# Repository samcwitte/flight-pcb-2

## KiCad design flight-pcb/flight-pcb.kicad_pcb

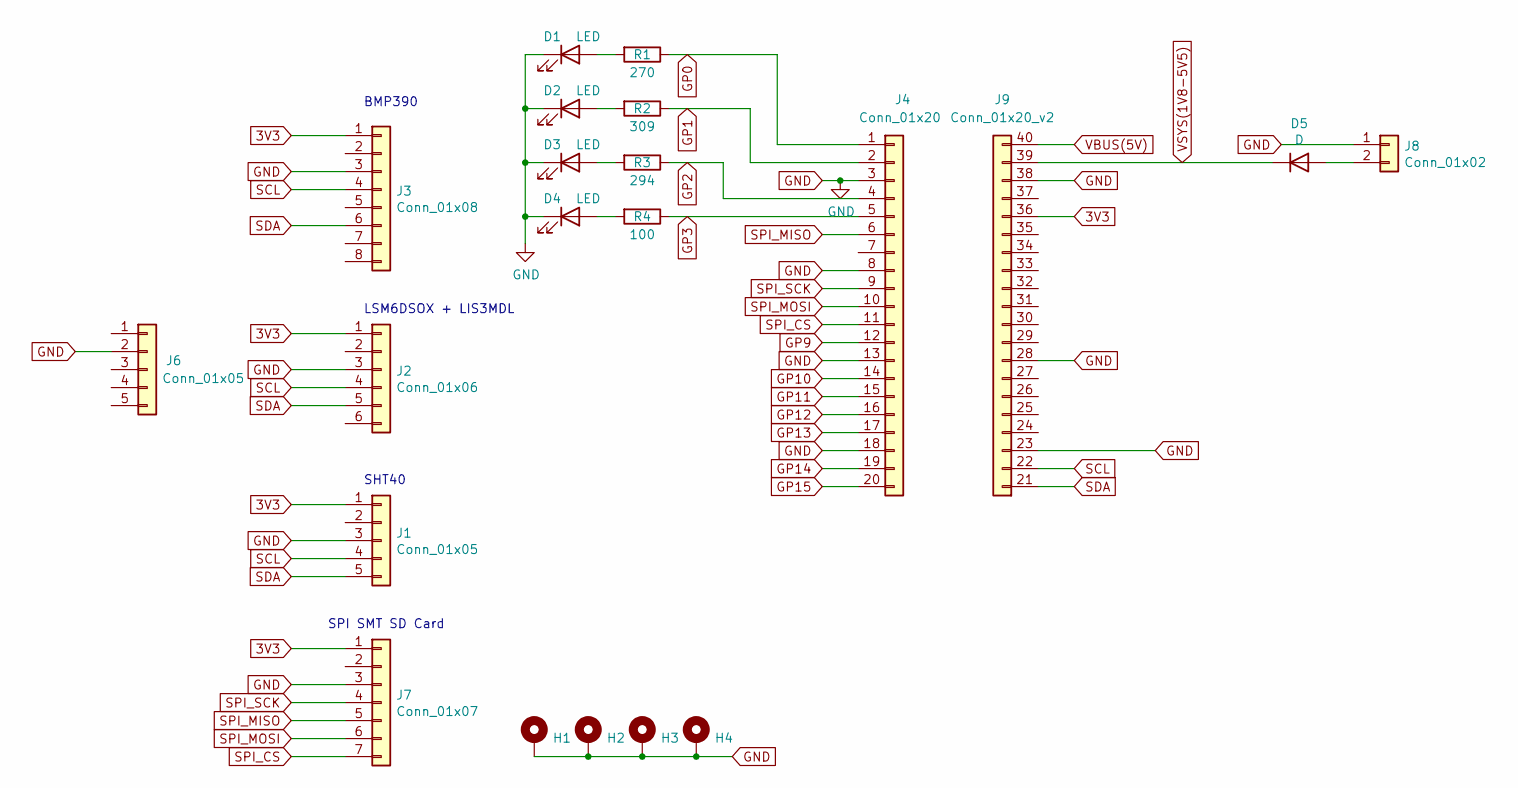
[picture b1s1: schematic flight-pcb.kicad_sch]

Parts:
D1, D2, D3, D4: LED; LED_0603_1608Metric
D5: D; D_SOD-123F
H1, H2, H3, H4: MountingHole_Pad; MountingHole_2.5mm_Pad
J1, J6: Conn_01x05; PinHeader_1x05_P2.54mm_Vertical
J2: Conn_01x06; PinHeader_1x06_P2.54mm_Vertical
J3: Conn_01x08; PinHeader_1x08_P2.54mm_Vertical
J4: Conn_01x20; PinHeader_1x20_P2.54mm_Vertical
J7: Conn_01x07; PinHeader_1x07_P2.54mm_Vertical
J8: Conn_01x02; JST_PH_S2B-PH-SM4-TB_1x02-1MP_P2.00mm_Horizontal
J9: Conn_01x20_v2; PinHeader_1x20_v2_P2.54mm_Vertical
R1: 270; R_0603_1608Metric
R2: 309; R_0603_1608Metric
R3: 294; R_0603_1608Metric
R4: 100; R_0603_1608Metric

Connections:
3V3: J1.1, J2.1, J3.1, J7.1, J9.36 (Pin_16)
GND: D1.1 (K), D2.1 (K), D3.1 (K), D4.1 (K), H1.1, H2.1, H3.1, H4.1, J1.3, J2.3, J3.3, J4.3, J4.8, J4.13, J4.18, J6.2, J7.3, J8.1, J9.23 (Pin_3), J9.28 (Pin_8), J9.38 (Pin_18)
GP0: J4.1, R1.1
GP1: J4.2, R2.1
GP2: J4.4, R3.1
GP3: J4.5, R4.1
GP9: J4.12
GP10: J4.14
GP11: J4.15
GP12: J4.16
GP13: J4.17
GP14: J4.19
GP15: J4.20
unnamed: D1.2 (A), R1.2
unnamed: D2.2 (A), R2.2
unnamed: D3.2 (A), R3.2
unnamed: D4.2 (A), R4.2
unnamed: D5.2 (A), J8.2
SCL: J1.4, J2.4, J3.4, J9.22 (Pin_2)
SDA: J1.5, J2.5, J3.6, J9.21 (Pin_1)
SPI_CS: J4.11, J7.7
SPI_MISO: J4.6, J7.5
SPI_MOSI: J4.10, J7.6
SPI_SCK: J4.9, J7.4
VBUS(5V): J9.40 (Pin_20)
VSYS(1V8-5V5): D5.1 (K), J9.39 (Pin_19)

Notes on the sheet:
SPI SMT SD Card
SHT40
BMP390
LSM6DSOX + LIS3MDL

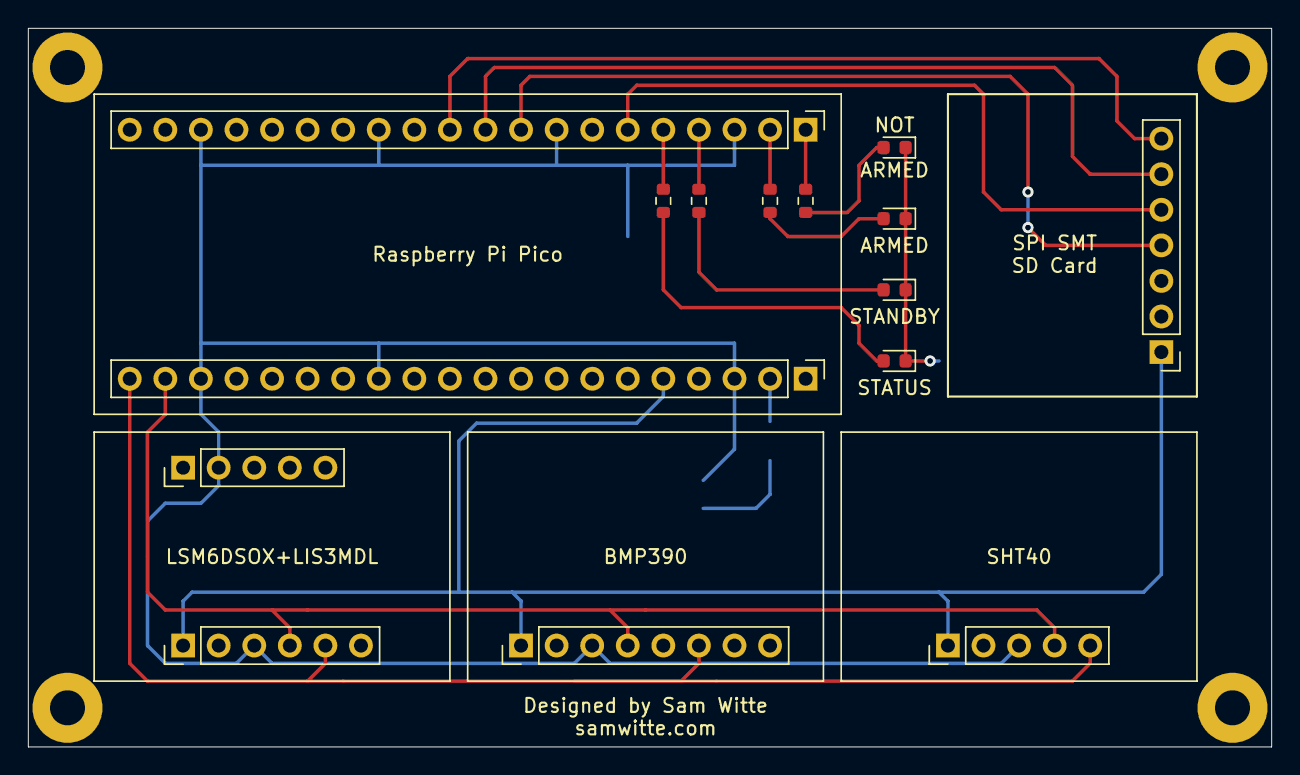
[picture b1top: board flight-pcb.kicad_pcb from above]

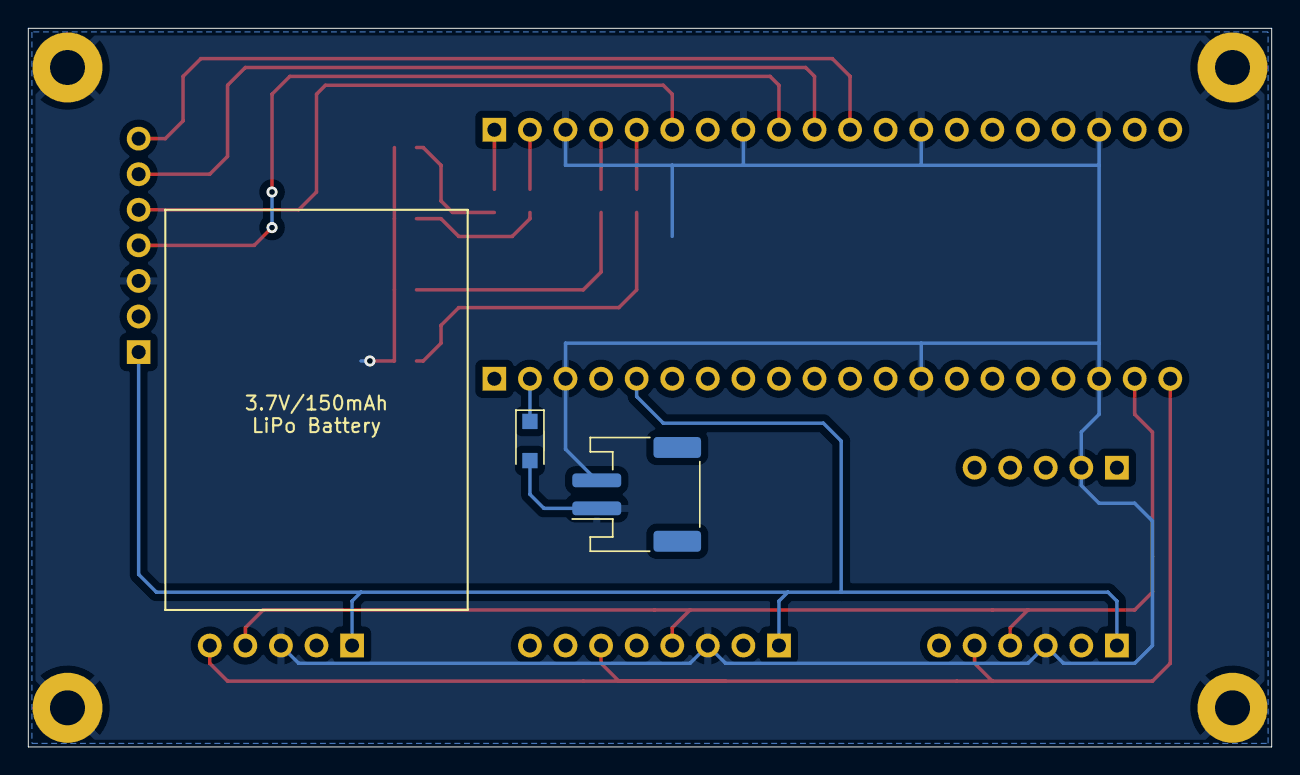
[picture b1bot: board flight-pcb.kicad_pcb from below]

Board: 2 copper layers, 88.8 x 51.3 mm, 21 parts (2 on the bottom side), 18 nets.

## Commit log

2022-09-13 updated project to KiCad V6.0
2022-09-15 updated raspberry pi header pins
    updated board to include new library with different pin numbers
